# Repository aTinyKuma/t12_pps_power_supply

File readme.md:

## 基于快充的小型电源转换板 
    快充输出经过boost升压至24V，给电络铁供电使用。
### 特性
- 支持100W快充诱骗
- 支持Boost至24V
- usb-c usb-a双口可选

### 选型
- 主芯片
    FS312H芯片 2元左右
- boost芯片 XL6019

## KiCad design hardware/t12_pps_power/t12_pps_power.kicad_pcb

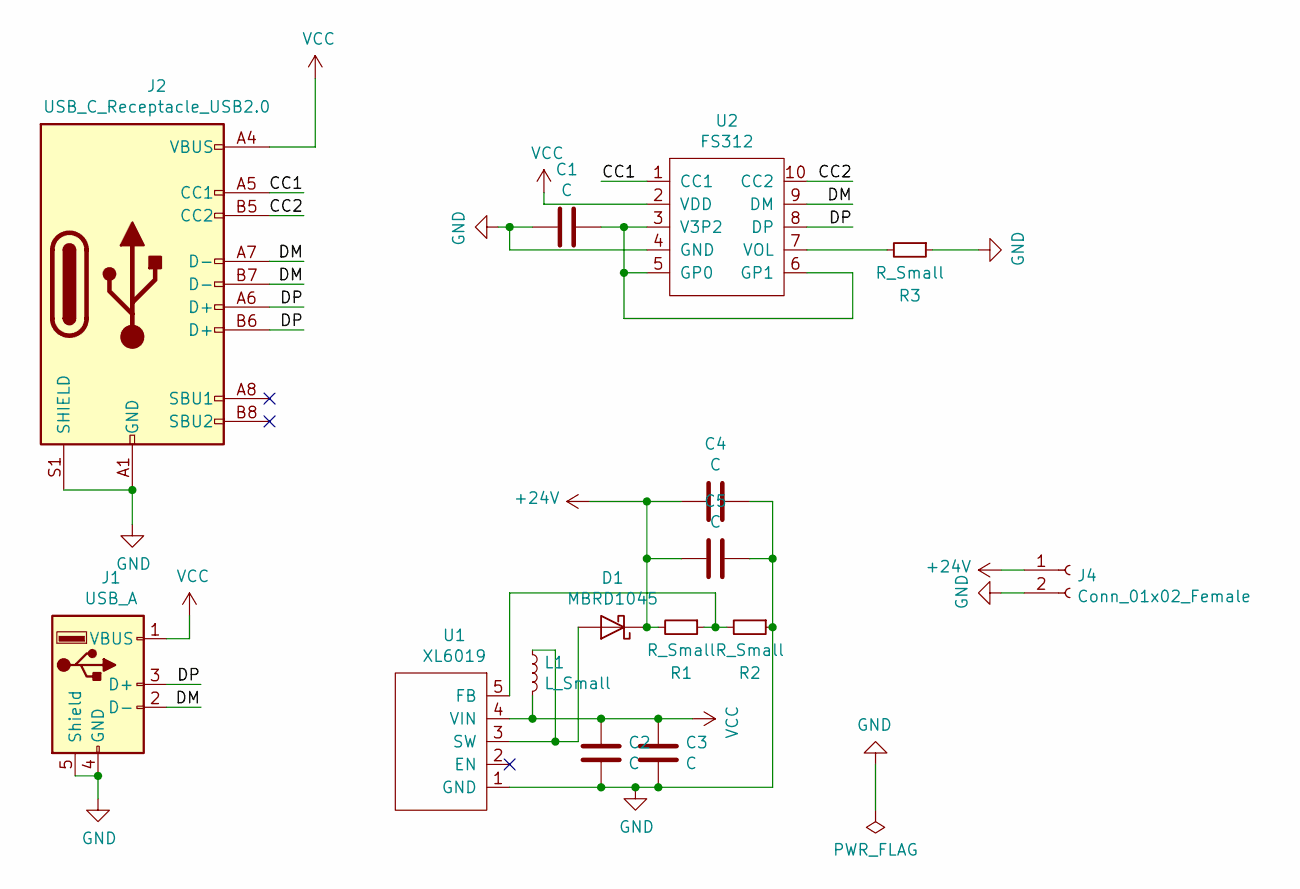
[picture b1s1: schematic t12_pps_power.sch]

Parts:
C1, C3, C5: C; C_0805_2012Metric_Pad1.18x1.45mm_HandSolder
C2, C4: C; CP_Elec_6.3x7.7
D1: MBRD1045; D_SMA
J1: USB_A; USB-A_VOOC_OPPO
J2: USB_C_Receptacle_USB2.0; USB_C_Receptacle_XKB_U262-16XN-4BVC11
J4: Conn_01x02_Female; JST_VH_B2P-VH_1x02_P3.96mm_Vertical
L1: L_Small; L_Wuerth_HCI-1040
R1, R2, R3: R_Small; R_0805_2012Metric_Pad1.20x1.40mm_HandSolder
U1: XL6019; TO-263-5_TabPin3
U2: FS312; SSOP-10_3.9x4.9mm_P1.00mm

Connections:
+24V: C4.1, C5.1, D1.1 (K), J4.1, R1.2
/CC1: J2.A5 (CC1), U2.1 (CC1)
/CC2: J2.B5 (CC2), U2.10 (CC2)
/DM: J1.2 (D-), J2.A7 (D-), J2.B7 (D-), U2.9 (DM)
/DP: J1.3 (D+), J2.A6 (D+), J2.B6 (D+), U2.8 (DP)
GND: C1.2, C2.1, C3.1, C4.2, C5.2, J1.4 (GND), J1.5 (Shield), J2.A1 (GND), J2.A12 (GND), J2.B1 (GND), J2.B12 (GND), J2.S1 (SHIELD), J4.2, R2.1, R3.1, U1.1 (GND), U2.4 (GND)
unnamed: C1.1, U2.3 (V3P2), U2.5 (GP0), U2.6 (GP1)
unnamed: D1.2 (A), L1.1, U1.3 (SW)
unnamed: R1.1, R2.2, U1.5 (FB)
unnamed: R3.2, U2.7 (VOL)
VCC: C2.2, C3.2, J1.1 (VBUS), J2.A4 (VBUS), J2.A9 (VBUS), J2.B4 (VBUS), J2.B9 (VBUS), L1.2, U1.4 (VIN), U2.2 (VDD)

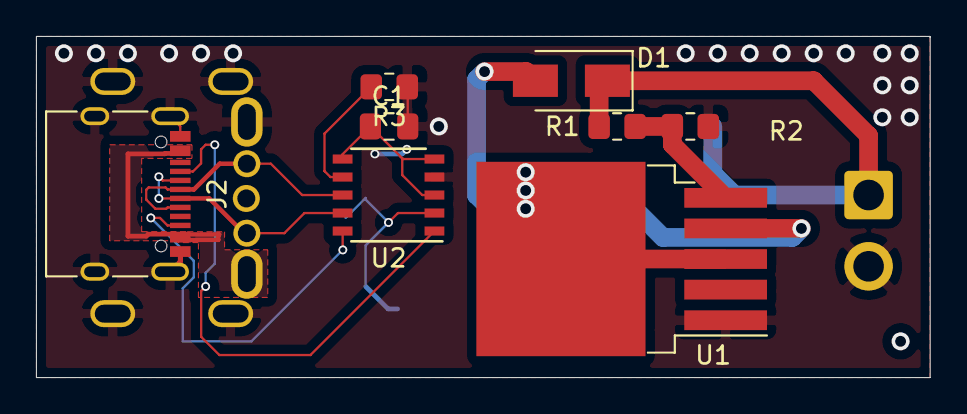
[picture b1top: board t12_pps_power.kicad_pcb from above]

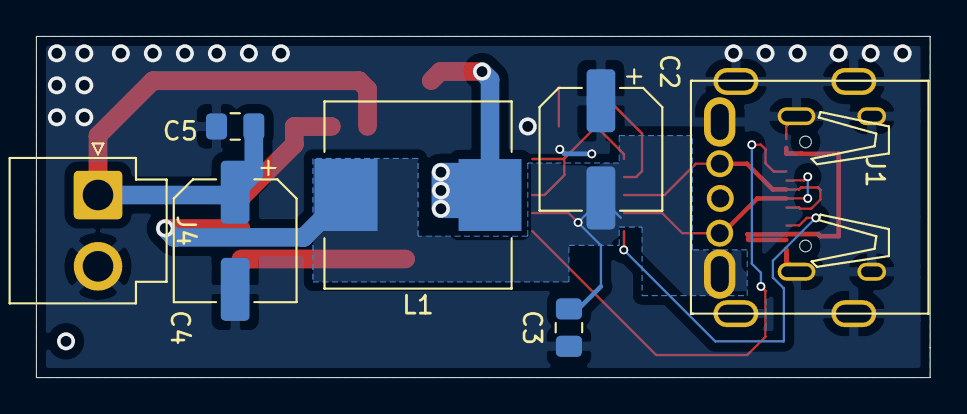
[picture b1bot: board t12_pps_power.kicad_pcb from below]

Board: 2 copper layers, 49.6 x 19.0 mm, 15 parts (7 on the bottom side), 11 nets.

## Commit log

2021-04-26 add readme
2021-04-28 change readme
2021-05-01 finish PCB Layout
2021-05-05 complete hardware V0.1
